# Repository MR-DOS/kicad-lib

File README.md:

# kicad-lib
----
## Intro
KiCad libraries made by me for myself, use under GPLv3 license.
The library is synchronised against my personal Inventree instance, so datasheets all point to that server which is currently not available for public, but if you need some datasheet, send me a message. Additional information is included, for example informing whether the part is active or discontinued.
----
## Prefixes
Symbols use prefixes in [ ] brackets to allow easier orientation, some of these may be combined together. These prefixes are:
1) "" (blank) - active component, no problems
2) Template - component may not be used, it is just a template for other active parts
3) NRND - this component is either marked as NRND by manufacturer, cannot be bought now (or frequently), may be simply bad or are difficult to get ahold of without running into a fake
4) NRND footprint - footprint has been used, but it is advised not to ever use it again
5) Obsolete - this components has been obsoleted by the manufacturer
6) Disabled - this component may not be used under any circumstances, reason included in the prefix (may be just a missing footprint)

### Additional prefixes for Disabled state
Added tags to "Disabled" prefix to further clarify or expand the reasons why it is disabled:
1) Not present in Inventree - non-inventarised part
2) Missing footprint - no footprint in library
3) Obsolete/Template - the same as above, just to clarify
----
## Final remarks
It is highly recommended that only parts with no prefix are used in any project (or [Template] to make a new part, but not used itself). Using any other is likely to cause problems - wrong footprint, untested behaviour, unability to obtain the component, fake component or the part being discontinued.
Absolutely no warranty is to be expected for the parts - use with caution and if you can, check that pinouts are correct and that the footprint matches the component (for example by printing on a paper).

In other branches, you may find old libraries meant for KiCAD v5 (I recommend you against using them, these should be treated as not checked).

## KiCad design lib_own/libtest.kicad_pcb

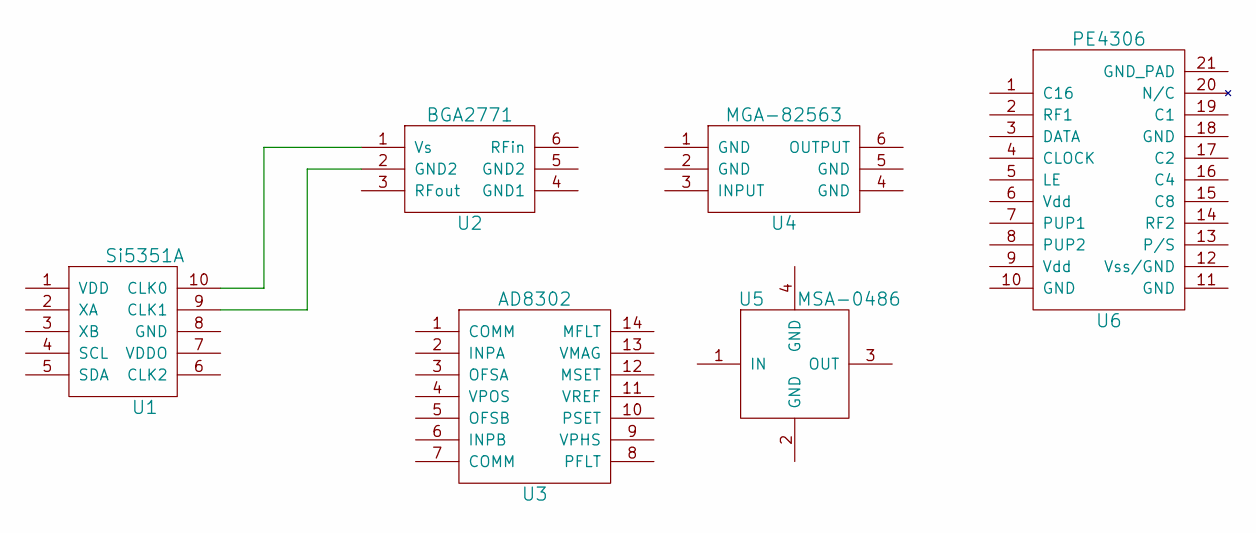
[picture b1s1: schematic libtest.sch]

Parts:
U1: Si5351A; MSOP-10_3x3mm_Pitch0.5mm
U2: BGA2771; SOT363(TSSOP6)
U3: AD8302; TSSOP-14_4.4x5mm_Pitch0.65mm
U4: MGA-82563; SOT363(TSSOP6)
U5: MSA-0486; 86_PLASTIC_PACKAGE
U6: PE4306; QFN-20-1EP_4x4mm_Pitch0.5mm

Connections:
unnamed: U1.9 (CLK1), U2.2 (GND2)
unnamed: U1.10 (CLK0), U2.1 (Vs)

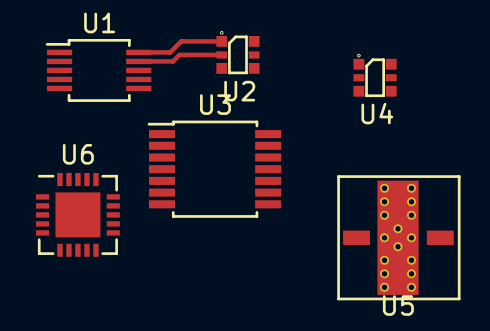
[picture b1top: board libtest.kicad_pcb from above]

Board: 2 copper layers, 6 parts (0 on the bottom side), 2 nets.

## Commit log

2018-01-04 Initial library commit
2018-01-04 Initial readme commit
2021-12-16 Removed old libraries, added new ones.
2021-12-17 Added new libraries
2021-12-17 deleted autogenerated file
2021-12-30 Fixes to components used in MWGEN-G1
2022-01-02 Added 300mA version of XC6204
2023-03-08 Updated library, synchronized data with Inventree
2023-03-08 Synchronised with Inventree, corrected old symbols
2023-03-08 Synchronised with HS_OSCILLOSCOPE-G1
2023-03-13 Added symbols
2023-03-14 Added all devices from guitar_down_octave
2023-03-16 Added devices from all projects, starting with recovery of old libraries which broke due to bug in v6-nightly (rounding of coordinates).
2023-03-16 Started merging old library before v6 rounding bug (currently stopped at ICS501).
2023-03-19 Merged with old v6 nightly non-broken library (before the rounding bug).
2023-03-20 Merged with old v6 nightly library (broken due to rounding bug). Footprints need checking.
2023-03-20 Add license info
2023-03-20 Fixed README
2023-03-21 Corrected all invisible fields, corrections to symbols and datasheet links
